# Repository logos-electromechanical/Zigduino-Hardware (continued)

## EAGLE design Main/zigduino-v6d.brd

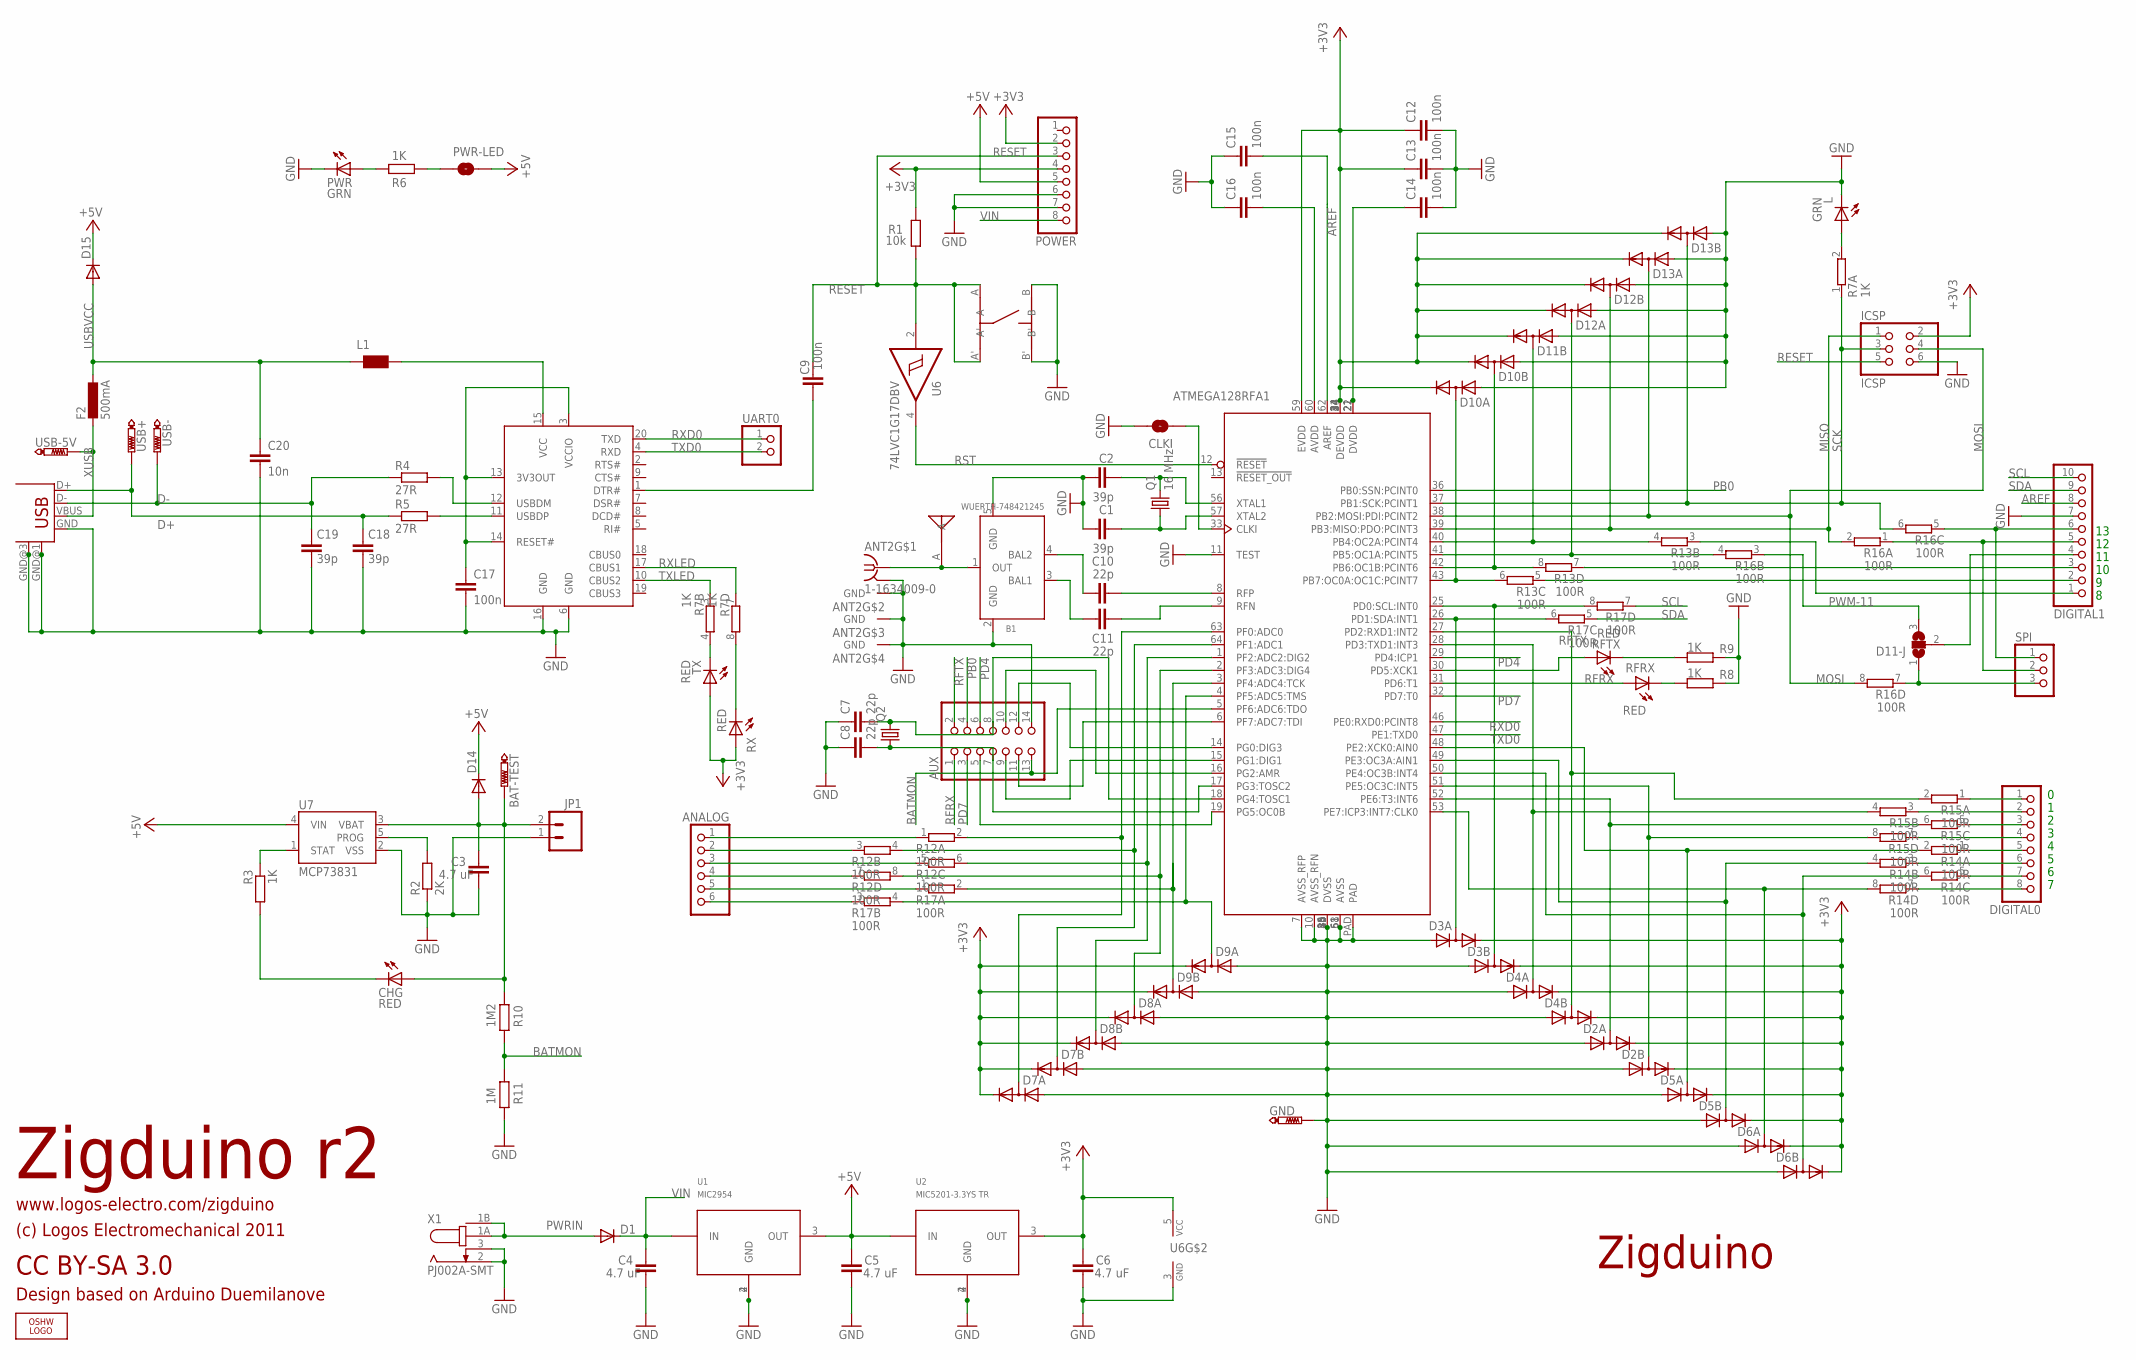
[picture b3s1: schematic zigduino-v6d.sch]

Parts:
ANALOG: PINHD-1X6; 1X06; PARTNO 19742
ANT1: MOLEX-ANT; PARTNO 0479480001
ANT2: 1-1634009-0; MMCX-THRU
AUX: PINHD-2X7_2.00; 2X07M; PARTNO 00217
B1: WUERTH-748421245; WURTH-BALUN; PARTNO 748421245
BAT-TEST: PTR1TP13SQ; TP13SQ; PARTNO TP13
C1, C2, C18, C19: 39p; C0603; PARTNO C1608C0G1H390J
C3, C4, C5, C6: 4.7 uF; C1206; PARTNO C3216Y5V1H475Z
C7, C8, C10, C11: 22p; C0603; PARTNO GQM1885C1H220JB01D
C9, C12, C13, C14, C15, C16, C17: 100n; C0603; PARTNO CC0603MRY5V9BB104
C20: 10n; C0603; PARTNO GRM188R71H103KA01D
CHG: RED; CHIP-LED0603; PARTNO LTST-C193KRKT-5A
CLKI: SOLDERJUMPERTRACE; SJ_2S-TRACE
D1, D14, D15: DIODE-SMB; SMB; PARTNO B150B-13-F
D2, D3, D4, D5, D6, D7, D8, D9, D10, D11, D12, D13: SD103ASDM; SOT26; PARTNO SD103ASDM-7
D11-J: SJ2W; SJ_2; PARTNO SJ3
DIGITAL0: PINHD-1X8; 1X08; PARTNO 19743
DIGITAL1: PINHD-1X10; 1X10; PARTNO 20083
F2: 500mA; L1812; PARTNO MF-MSMF050-2
GND: PTR1TP13SQ; TP13SQ; PARTNO TP13
ICSP: ICSP; 2X03; PARTNO 961206-6404-AR
JP1: M02-JST-2MM-SMT; S2B-PH; PARTNO S2B-PH-SM4-TB(LF)(SN)
L: GRN; CHIP-LED0603; PARTNO LTST-C193KGKT-5A
L1: WE-CBF_0805; 0805; PARTNO MI0805K400R-10
LOGO1: OSHW_LOGO_FILLX0200-NT; OSHW_FILLX200_NOTEXT
POWER: PINHD-1X8; 1X08; PARTNO 19743
PWR: GRN; CHIP-LED0603; PARTNO LTST-C193KGKT-5A
PWR-LED: SOLDERJUMPERTRACE; SJ_2S-TRACE
Q1: 16 MHz; CSM-3X; PARTNO ECS-160-20-3X-TR
Q2: CRYSTALTC26H; TC26H
R1: 10k; R0603; PARTNO RMCF0603FT10K0
R2: 2K; R0603; PARTNO RC0603FR-072KL
R3, R6, R8, R9: 1K; R0603; PARTNO RMCF0603FT1K00
R4, R5: 27R; R0603; PARTNO RC0603JR-0727RL
R7: 1K; CTS742C083-RES; PARTNO 742C083102JPTR
R10: 1M2; R0603; PARTNO ERJ-3EKF1204V
R11: 1M; R0603; PARTNO ERJ-3EKF1004V
R12, R13, R14, R15, R16, R17: 100R; CTS742C083-RES; PARTNO 742C083101JPTR
RFRX: RED; CHIP-LED0603; PARTNO LTST-C193KRKT-5A
RFTX: RED; CHIP-LED0603; PARTNO LTST-C193KRKT-5A
RX: RED; CHIP-LED0603; PARTNO LTST-C193KRKT-5A
SPI: PINHD-1X3; 1X03; PARTNO 20152
SW1: EVQ-PSD02K; EVQPSD02K; PARTNO EVQ-PSD02K
TX: RED; CHIP-LED0603; PARTNO LTST-C193KRKT-5A
U1: MIC2954; SOT223; PARTNO MIC2954-03WS-TR
U2: MIC5201-3.3YS TR; SOT223; PARTNO MIC5201-3.3YS TR
U3: ATMEGA128RFA1; QFN64; PARTNO ATMEGA128RFA1-ZUR
U4: FT231XS-R; SSOP20; PARTNO FT231XS-R
U6: 74LVC1G17DBV; SOT23-5; PARTNO SN74LVC1G17DBVR
U7: MCP73831; SOT23-5; PARTNO MCP73831T-2ACI/OT
UART0: PINHD-1X2; 1X02; PARTNO 00522
USB: USB-MB-S; PARTNO 20236
USB+: PTR1TP13SQ; TP13SQ; PARTNO TP13
USB-, USB-5V: PTR1TP13SQ; TP13SQ; PARTNO TP13
X1: PJ002A-SMT; PARTNO PJ-002AH-SMT

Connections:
+3V3: C6.1, C12.1, C13.1, D2.2 (C), D2.5 (C), D3.2 (C), D3.5 (C), D4.2 (C), D4.5 (C), D5.2 (C), D5.5 (C), D6.2 (C), D6.5 (C), D7.2 (C), D7.5 (C), D8.2 (C), D8.5 (C), D9.2 (C), D9.5 (C), D10.2 (C), D10.5 (C), D11.5 (C), D12.2 (C), D12.5 (C), D13.2 (C), D13.5 (C), ICSP.2, POWER.2, POWER.4, R1.2, RX.A, TX.A, U2.3 (OUT), U3.23 (DEVDD), U3.34 (DEVDD), U3.44 (DEVDD), U3.54 (DEVDD), U3.59 (EVDD), U6.5 (VCC)
+5V: C5.1, D14.C, D15.C, POWER.5, PWR-LED.2, U1.3 (OUT), U2.1 (IN), U7.4 (VIN)
AREF: C15.2, DIGITAL1.8, U3.62 (AREF)
BATMON: AUX.13, R10.2, R11.1, U3.5 (PF6:ADC6:TDO)
D+: C18.1, R5.1, USB.D+, USB+.TP
D-: C19.1, R4.1, USB.D-, USB-.TP
DTR: C9.1, U4.1 (DTR#)
GND: ANT2.G@0 (GND), ANT2.G@1 (GND), ANT2.G@2 (GND), ANT2.G@3 (GND), AUX.14, B1.2 (GND), B1.5 (GND), C1.1, C2.1, C3.2, C4.2, C5.2, C6.2, C7.1, C8.1, C12.2, C13.2, C14.2, C15.1, C16.1, C17.2, C18.2, C19.2, C20.2, CLKI.2, D2.3 (A), D2.6 (A), D3.3 (A), D3.6 (A), D4.3 (A), D4.6 (A), D5.3 (A), D5.6 (A), D6.3 (A), D6.6 (A), D7.3 (A), D7.6 (A), D8.3 (A), D8.6 (A), D9.3 (A), D9.6 (A), D10.3 (A), D10.6 (A), D11.6 (A), D12.3 (A), D12.6 (A), D13.3 (A), D13.6 (A), DIGITAL1.7, GND.TP, ICSP.6, JP1.1, L.C, POWER.6, POWER.7, PWR.C, R2.1, R8.1, R9.1, R11.2, SW1.B, SW1.B', U1.2 (GND), U1.4 (GND), U2.2 (GND), U2.4 (GND), U3.7 (AVSS_RFP), U3.10 (AVSS_RFN), U3.11 (TEST), U3.20 (DVSS), U3.24 (DVSS), U3.35 (DVSS), U3.45 (DVSS), U3.55 (DVSS), U3.58 (AVSS), U3.61 (AVSS), U3.PAD, U4.6 (GND), U4.16 (GND), U6.3 (GND), U7.2 (VSS), USB.GND, USB.GND@1 (GND), USB.GND@3 (GND), X1.2, X1.3
MISO: D12.1 (AC), ICSP.1, R16.2, U3.39 (PB3:MISO:PDO:PCINT3)
MOSI: D13.4 (AC), ICSP.4, R16.8 (2), U3.38 (PB2:MOSI:PDI:PCINT2)
MOSI-PIN: D11-J.1, R16.7 (1), SPI.3
unnamed: R9.2, RFTX.C
unnamed: L.A, R7.2
unnamed: PWR.A, R6.2
unnamed: B1.4 (BAL2), C10.1
unnamed: DIGITAL0.3, R15.5 (1)
unnamed: C1.2, Q1.1, U3.57 (XTAL2)
unnamed: C2.2, Q1.2, U3.56 (XTAL1)
unnamed: PWR-LED.1, R6.1
unnamed: B1.3 (BAL1), C11.1
unnamed: DIGITAL1.5, R16.1, SPI.2
unnamed: DIGITAL0.5, R14.1
unnamed: DIGITAL0.7, R14.5 (1)
unnamed: DIGITAL0.6, R14.3 (1)
unnamed: DIGITAL0.4, R15.7 (1)
unnamed: DIGITAL0.8, R14.7 (1)
unnamed: D3.1 (AC), R17.8 (2), U3.25 (PD0:SCL:INT0)
unnamed: D3.4 (AC), R17.6 (2), U3.26 (PD1:SDA:INT1)
unnamed: ANT1.A, ANT2.C (1), B1.1 (OUT)
unnamed: D12.4 (AC), R16.4 (2), U3.41 (PB5:OC1A:PCINT5)
unnamed: R8.2, RFRX.C
unnamed: D2.4 (AC), R15.6 (2), U3.52 (PE6:T3:INT6)
unnamed: D2.1 (AC), R15.8 (2), U3.51 (PE5:OC3C:INT5)
unnamed: C10.2, U3.8 (RFP)
unnamed: C11.2, U3.9 (RFN)
unnamed: DIGITAL1.6, R16.5 (1), SPI.1
unnamed: R2.2, U7.5 (PROG)
unnamed: R3.1, U7.1 (STAT)
unnamed: R7.4 (2), TX.C
unnamed: CHG.C, R3.2
unnamed: C17.1, U4.3 (VCCIO), U4.13 (3V3OUT), U4.14 (RESET#)
unnamed: R7.8 (2), RX.C
unnamed: D11.1 (AC), R13.4 (2), U3.40 (PB4:OC2A:PCINT4)
unnamed: CLKI.1, U3.33 (CLKI)
unnamed: R4.2, U4.12 (USBDM)
unnamed: R5.2, U4.11 (USBDP)
unnamed: L1.2, U4.15 (VCC)
unnamed: D10.1 (AC), R13.8 (2), U3.42 (PB6:OC1B:PCINT6)
unnamed: D10.4 (AC), R13.6 (2), U3.43 (PB7:OC0A:OC1C:PCINT7)
unnamed: D5.4 (AC), R14.2, U3.48 (PE2:XCK0:AIN0)
unnamed: D6.1 (AC), R14.6 (2), U3.50 (PE4:OC3B:INT4)
unnamed: D5.1 (AC), R14.4 (2), U3.49 (PE3:OC3A:AIN1)
unnamed: D6.4 (AC), R14.8 (2), U3.53 (PE7:ICP3:INT7:CLK0)
unnamed: ANALOG.5, R17.1
unnamed: ANALOG.6, R17.3 (1)
unnamed: AUX.11, U3.6 (PF7:ADC7:TDI)
unnamed: D7.4 (AC), R12.2, U3.63 (PF0:ADC0)
unnamed: D7.1 (AC), R12.4 (2), U3.64 (PF1:ADC1)
unnamed: D8.1 (AC), R12.6 (2), U3.1 (PF2:ADC2:DIG2)
unnamed: D8.4 (AC), R12.8 (2), U3.2 (PF3:ADC3:DIG4)
unnamed: D9.1 (AC), R17.2, U3.3 (PF4:ADC4:TCK)
unnamed: D9.4 (AC), R17.4 (2), U3.4 (PF5:ADC5:TMS)
unnamed: ANALOG.1, R12.1
unnamed: ANALOG.2, R12.3 (1)
unnamed: ANALOG.3, R12.5 (1)
unnamed: ANALOG.4, R12.7 (1)
unnamed: DIGITAL1.1, R13.3 (1)
unnamed: D11-J.2, DIGITAL1.4
unnamed: AUX.12, U3.14 (PG0:DIG3)
unnamed: C14.1, U3.21 (DVDD), U3.22 (DVDD)
unnamed: C16.2, U3.60 (AVDD)
unnamed: DIGITAL1.2, R13.5 (1)
unnamed: DIGITAL0.1, R15.1
unnamed: DIGITAL0.2, R15.3 (1)
unnamed: AUX.9, U3.15 (PG1:DIG1)
unnamed: AUX.5, U3.19 (PG5:OC0B)
unnamed: AUX.8, C7.2, Q2.2, U3.18 (PG4:TOSC1)
unnamed: AUX.7, C8.2, Q2.1, U3.17 (PG3:TOSC2)
unnamed: AUX.10, U3.16 (PG2:AMR)
PB0: AUX.4, U3.36 (PB0:SSN:PCINT0)
PD4: AUX.6, U3.29 (PD4:ICP1)
PD7: AUX.3, U3.32 (PD7:T0)
PWM-10: DIGITAL1.3, R13.7 (1)
PWM-11: D11-J.3, R16.3 (1)
PWRIN: D1.A, X1.1A, X1.1B
RESET: C9.2, ICSP.5, POWER.3, R1.1, SW1.A, SW1.A', U6.2 (I)
RFRX: AUX.1, RFRX.A, U3.31 (PD6:T1)
RFTX: AUX.2, RFTX.A, U3.30 (PD5:XCK1)
RST: U3.12 (!RESET!), U6.4 (O)
RXD0: U3.46 (PE0:RXD0:PCINT8), U4.20 (TXD), UART0.1
RXD1: D4.1 (AC), R15.2, U3.27 (PD2:RXD1:INT2)
RXLED: R7.7 (1), U4.17 (CBUS1)
SCK: D13.1 (AC), ICSP.3, R7.1, R16.6 (2), U3.37 (PB1:SCK:PCINT1)
SCL: DIGITAL1.10, R17.7 (1)
SDA: DIGITAL1.9, R17.5 (1)
TXD0: U3.47 (PE1:TXD0), U4.4 (RXD), UART0.2
TXD1: D4.4 (AC), R15.4 (2), U3.28 (PD3:TXD1:INT3)
TXLED: R7.3 (1), U4.10 (CBUS2)
USBVCC: C20.1, D15.A, F2.1, L1.1
VBAT: BAT-TEST.TP, C3.1, CHG.A, D14.A, JP1.2, R10.1, U7.3 (VBAT)
VIN: C4.1, D1.C, POWER.8, U1.1 (IN)
XUSB: F2.2, USB.VBUS, USB-5V.TP

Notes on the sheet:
Zigduino r2
CC BY-SA 3.0
(c) Logos Electromechanical 2011
www.logos-electro.com/zigduino
ATMEGA128RFA1
Zigduino
Design based on Arduino Duemilanove

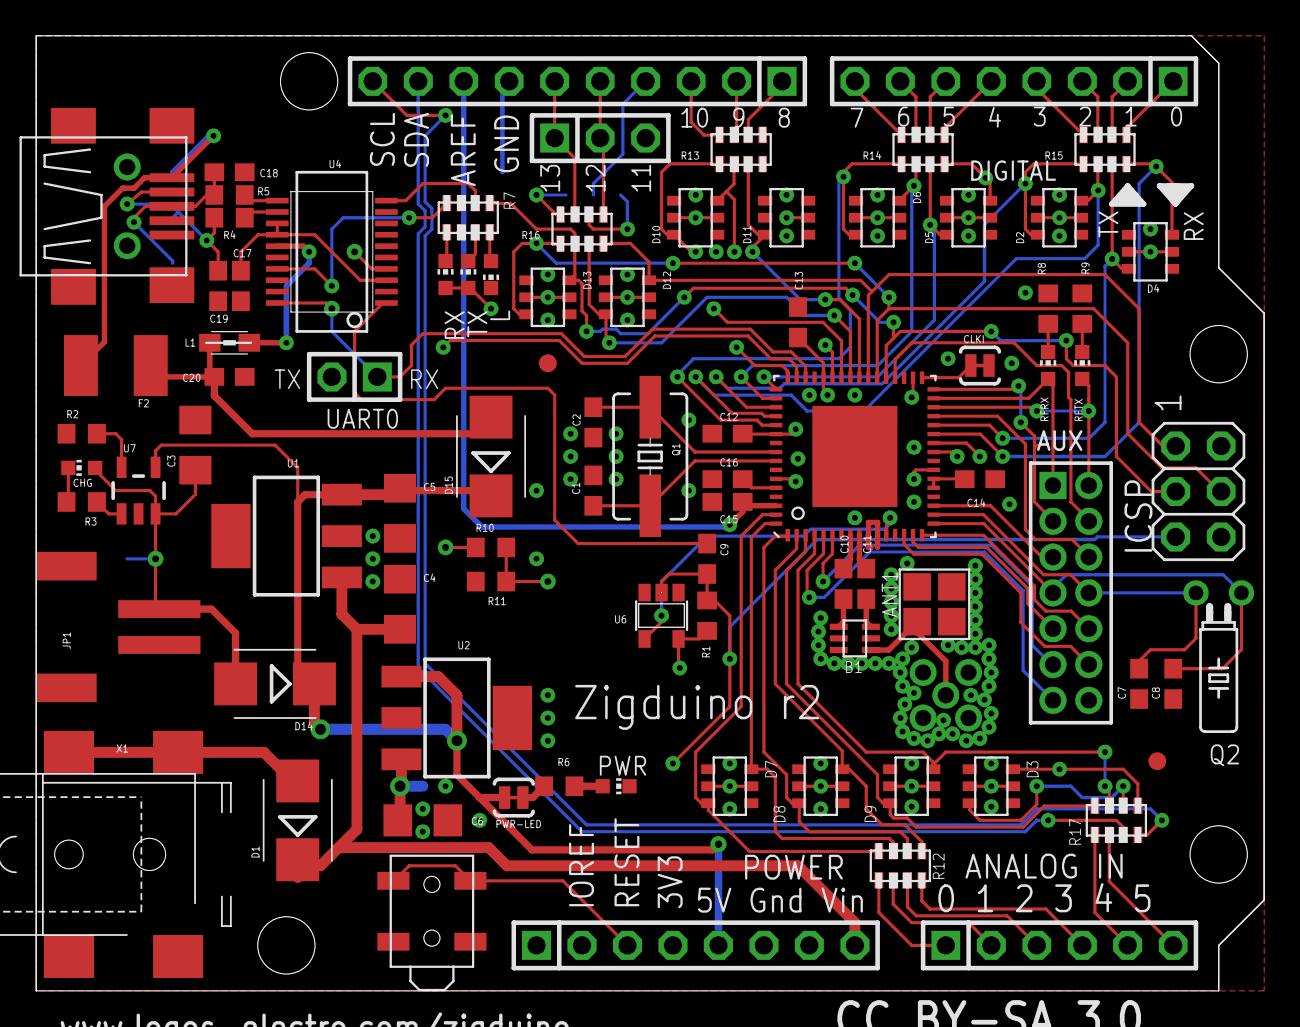
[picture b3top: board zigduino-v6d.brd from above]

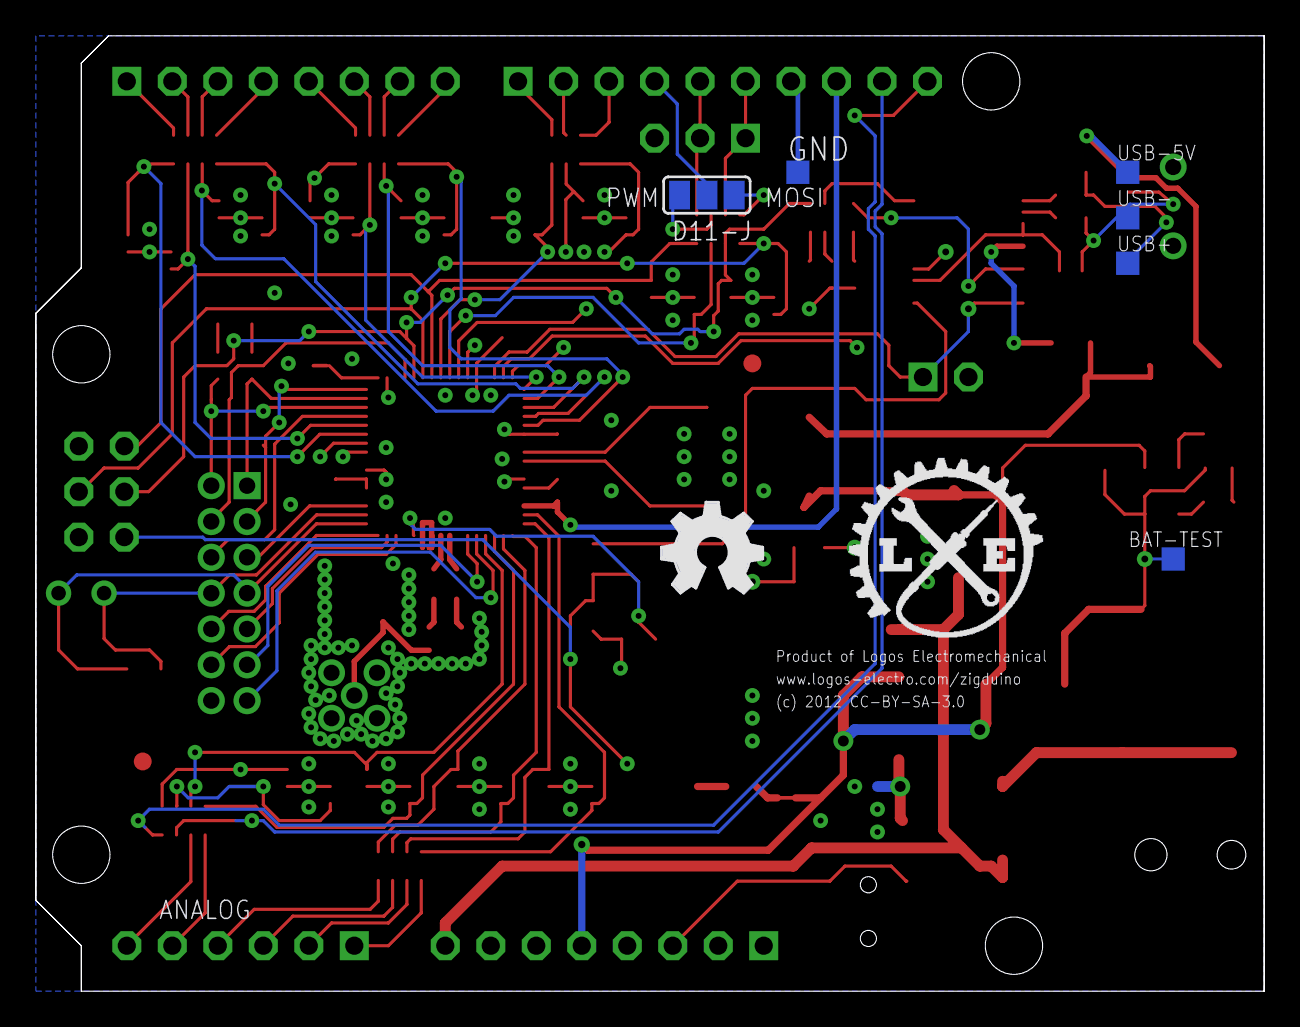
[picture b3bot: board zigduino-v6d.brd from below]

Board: 4 copper layers, 68.6 x 53.3 mm, 96 parts (8 on the bottom side), 102 nets.

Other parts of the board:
U$3, U$5: FIDUCIAL_G10
U$4: LOGO-SM

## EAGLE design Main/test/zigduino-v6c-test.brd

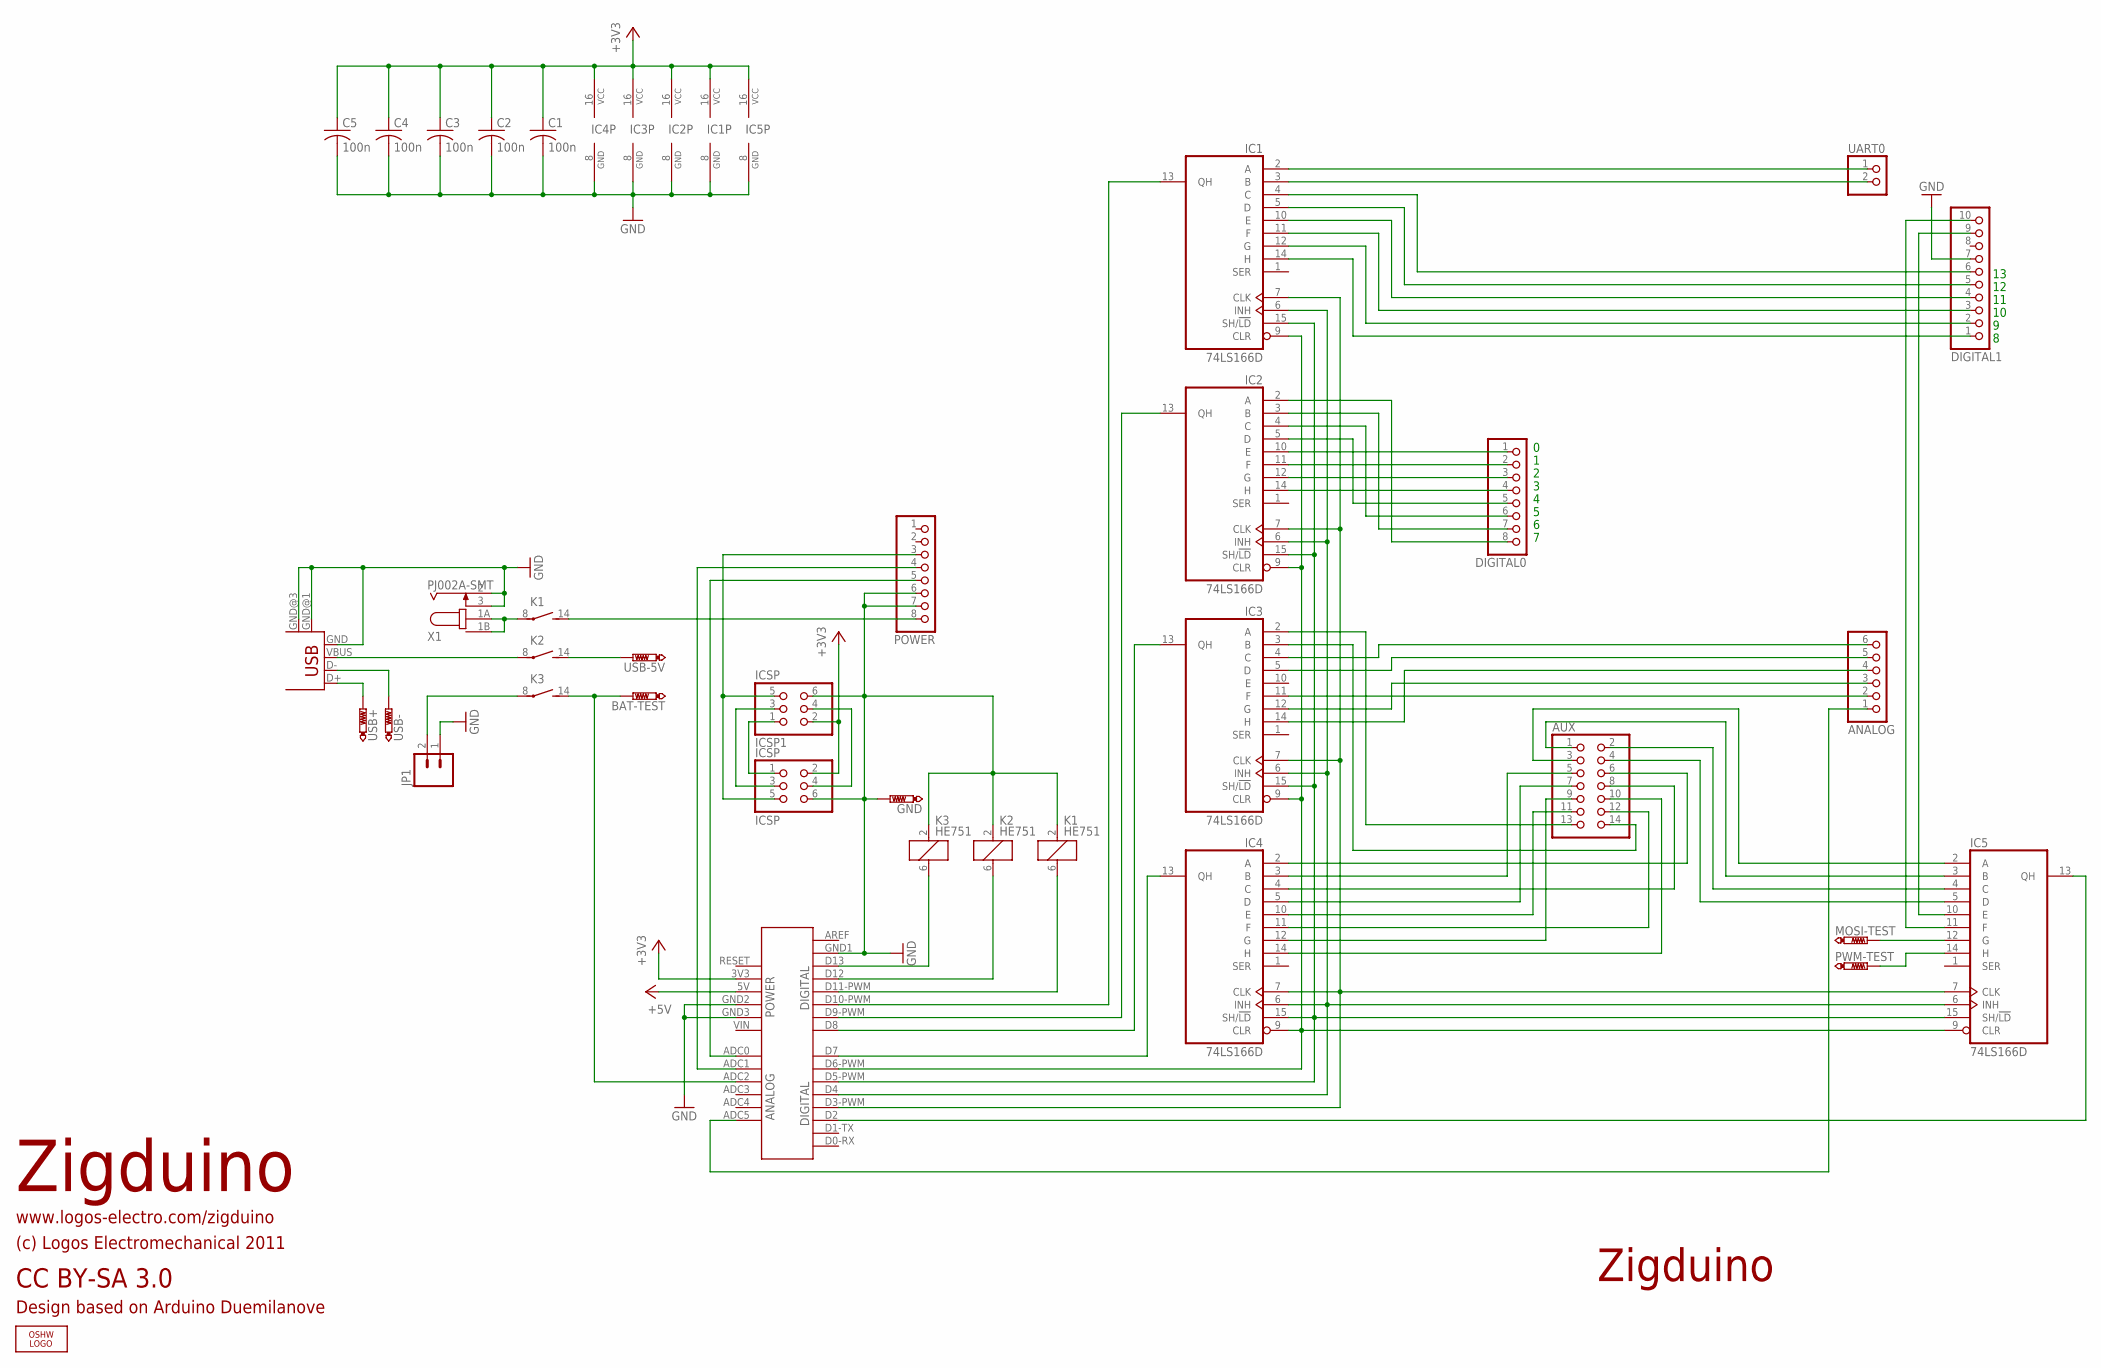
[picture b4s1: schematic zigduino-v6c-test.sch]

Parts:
ANALOG: PINHD-1X6; 1X06; PARTNO 19742
AUX: PINHD-2X7_2.00; 2X07M; PARTNO 00217
BAT-TEST: PTR1PAD1-13; P1-13; PARTNO TP13
C1, C2, C3, C4, C5: 100n; C0603
DIGITAL0: PINHD-1X8; 1X08; PARTNO 19743
DIGITAL1: PINHD-1X10; 1X10; PARTNO 20083
GND: PTR1PAD1-13; P1-13; PARTNO TP13
IC1, IC2, IC3, IC4, IC5: 74LS166D; SO16
ICSP, ICSP1: ICSP; 2X03; PARTNO 961206-6404-AR
JP1: M02-JST-2MM-SMT; S2B-PH
K1, K2, K3: HE751
LOGO1: OSHW_LOGO_FILLX0200-NT; OSHW_FILLX200_NOTEXT
MOSI-TEST: PTR1PAD1-13; P1-13; PARTNO TP13
POWER: PINHD-1X8; 1X08; PARTNO 19743
PWM-TEST: PTR1PAD1-13; P1-13; PARTNO TP13
SHIELD1: 2009
UART0: PINHD-1X2; 1X02; PARTNO 00522
USB1: USB-MB-S
USB+: PTR1PAD1-13; P1-13; PARTNO TP13
USB-, USB-5V: PTR1PAD1-13; P1-13; PARTNO TP13
X1: PJ002A-SMT

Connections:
+3V3: C1.1, C2.1, C3.1, C4.1, C5.1, IC1.16 (VCC), IC2.16 (VCC), IC3.16 (VCC), IC4.16 (VCC), IC5.16 (VCC), ICSP.2, ICSP1.2, SHIELD1.3V3
+5V: SHIELD1.5V
GND: C1.2, C2.2, C3.2, C4.2, C5.2, DIGITAL1.7, GND.TP, IC1.8 (GND), IC2.8 (GND), IC3.8 (GND), IC4.8 (GND), IC5.8 (GND), ICSP.6, ICSP1.6, JP1.1, K1.2 (1), K2.2 (1), K3.2 (1), POWER.6, POWER.7, SHIELD1.GND1, SHIELD1.GND2, SHIELD1.GND3, USB1.GND, USB1.GND@1 (GND), USB1.GND@3 (GND), X1.2, X1.3
unnamed: IC1.2 (A), UART0.1
unnamed: IC1.3 (B), UART0.2
unnamed: JP1.2, K3.8
unnamed: DIGITAL1.6, IC1.4 (C)
unnamed: DIGITAL1.5, IC1.5 (D)
unnamed: DIGITAL1.4, IC1.10 (E)
unnamed: DIGITAL1.3, IC1.11 (F)
unnamed: DIGITAL1.2, IC1.12 (G)
unnamed: DIGITAL1.1, IC1.14 (H)
unnamed: DIGITAL0.4, IC2.14 (H)
unnamed: DIGITAL0.3, IC2.12 (G)
unnamed: DIGITAL0.2, IC2.11 (F)
unnamed: DIGITAL0.1, IC2.10 (E)
unnamed: DIGITAL0.5, IC2.5 (D)
unnamed: DIGITAL0.6, IC2.4 (C)
unnamed: DIGITAL0.7, IC2.3 (B)
unnamed: DIGITAL0.8, IC2.2 (A)
unnamed: ANALOG.1, SHIELD1.ADC5
unnamed: ANALOG.6, IC3.4 (C)
unnamed: ANALOG.5, IC3.5 (D)
unnamed: ANALOG.4, IC3.14 (H)
unnamed: ANALOG.3, IC3.12 (G)
unnamed: ANALOG.2, IC3.11 (F)
unnamed: AUX.13, IC3.2 (A)
unnamed: AUX.14, IC3.3 (B)
unnamed: AUX.6, IC4.2 (A)
unnamed: AUX.5, IC4.3 (B)
unnamed: AUX.8, IC4.4 (C)
unnamed: AUX.7, IC4.5 (D)
unnamed: AUX.11, IC4.10 (E)
unnamed: AUX.12, IC4.11 (F)
unnamed: AUX.9, IC4.12 (G)
unnamed: AUX.3, IC5.2 (A)
unnamed: AUX.10, IC4.14 (H)
unnamed: AUX.2, IC5.4 (C)
unnamed: AUX.4, IC5.5 (D)
unnamed: AUX.1, IC5.3 (B)
unnamed: IC1.9 (CLR), IC2.9 (CLR), IC3.9 (CLR), IC4.9 (CLR), IC5.9 (CLR), SHIELD1.D6-PWM (D6)
unnamed: IC1.15 (SH/!LD), IC2.15 (SH/!LD), IC3.15 (SH/!LD), IC4.15 (SH/!LD), IC5.15 (SH/!LD), SHIELD1.D5-PWM (D5)
unnamed: IC1.6 (INH), IC2.6 (INH), IC3.6 (INH), IC4.6 (INH), IC5.6 (INH), SHIELD1.D4
unnamed: IC1.7 (CLK), IC2.7 (CLK), IC3.7 (CLK), IC4.7 (CLK), IC5.7 (CLK), SHIELD1.D3-PWM (D3)
unnamed: DIGITAL1.9, IC5.10 (E)
unnamed: DIGITAL1.10, IC5.11 (F)
unnamed: IC5.12 (G), MOSI-TEST.TP
unnamed: IC5.14 (H), PWM-TEST.TP
unnamed: IC1.13 (QH), SHIELD1.D10-PWM (D10)
unnamed: IC2.13 (QH), SHIELD1.D9-PWM (D9)
unnamed: IC3.13 (QH), SHIELD1.D8
unnamed: IC4.13 (QH), SHIELD1.D7
unnamed: IC5.13 (QH), SHIELD1.D2
unnamed: POWER.5, SHIELD1.ADC0
unnamed: POWER.4, SHIELD1.ADC1
unnamed: K1.14 (S), POWER.8
unnamed: K2.14 (S), USB-5V.TP
unnamed: BAT-TEST.TP, K3.14 (S), SHIELD1.ADC2
unnamed: K2.6 (2), SHIELD1.D12
unnamed: K1.6 (2), SHIELD1.D11-PWM (D11)
unnamed: ICSP.4, ICSP1.4
unnamed: K3.6 (2), SHIELD1.D13
unnamed: ICSP.1, ICSP1.1
unnamed: ICSP.3, ICSP1.3
unnamed: ICSP.5, ICSP1.5, POWER.3
unnamed: K2.8, USB1.VBUS
unnamed: USB1.D+, USB+.TP
unnamed: USB1.D-, USB-.TP
unnamed: K1.8, X1.1A, X1.1B

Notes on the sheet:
Zigduino
CC BY-SA 3.0
(c) Logos Electromechanical 2011
www.logos-electro.com/zigduino
Design based on Arduino Duemilanove

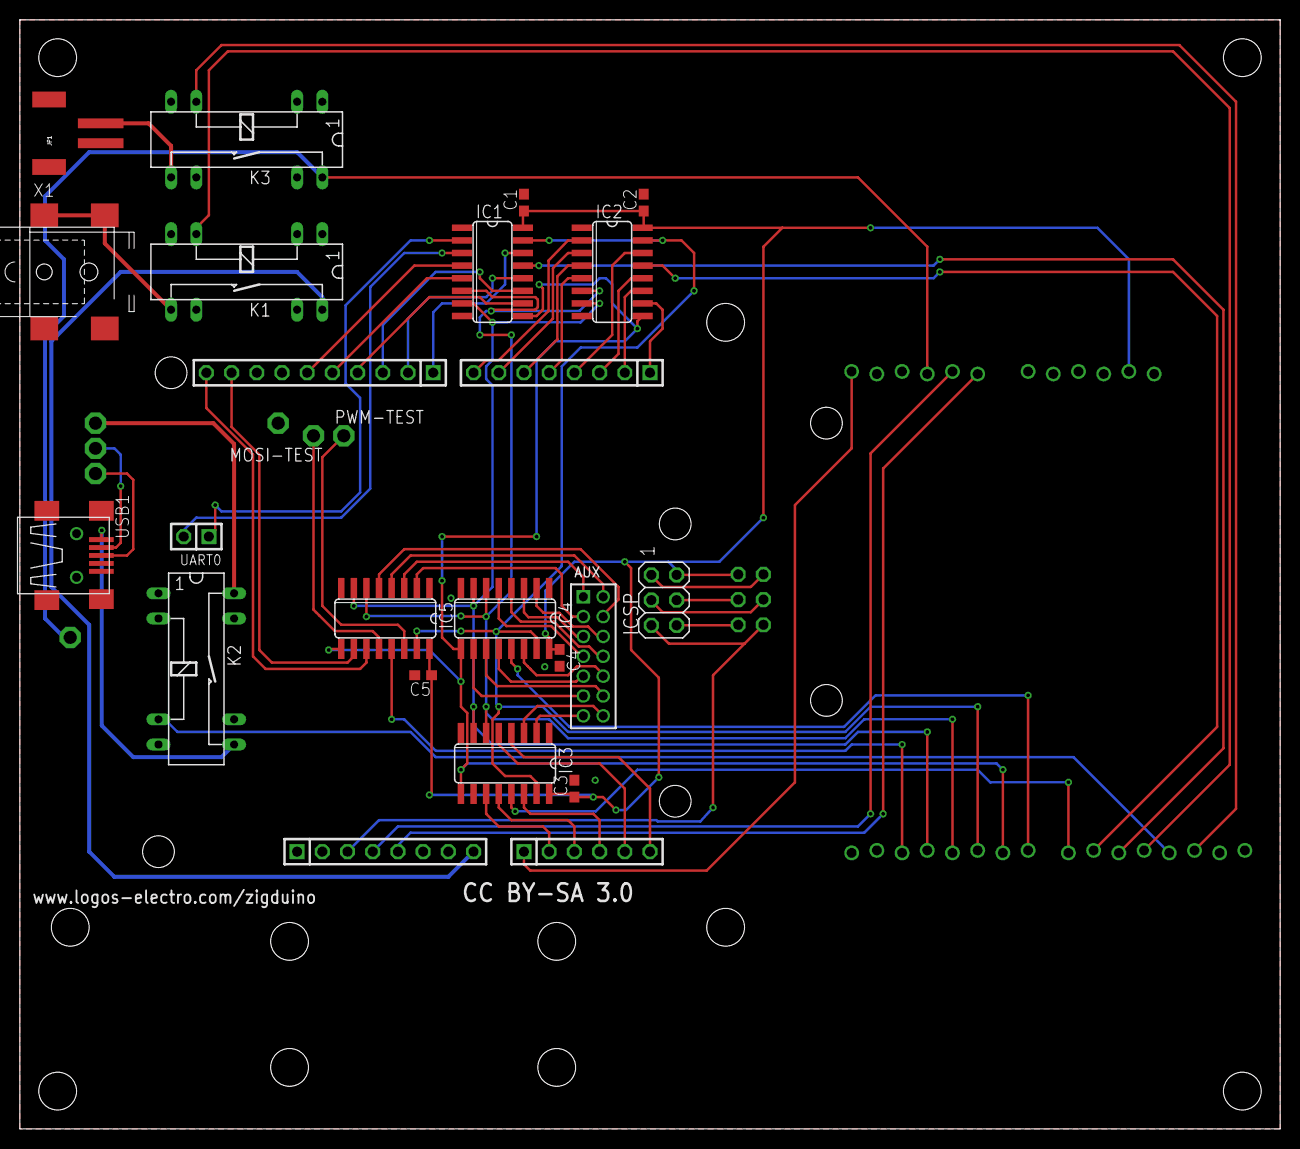
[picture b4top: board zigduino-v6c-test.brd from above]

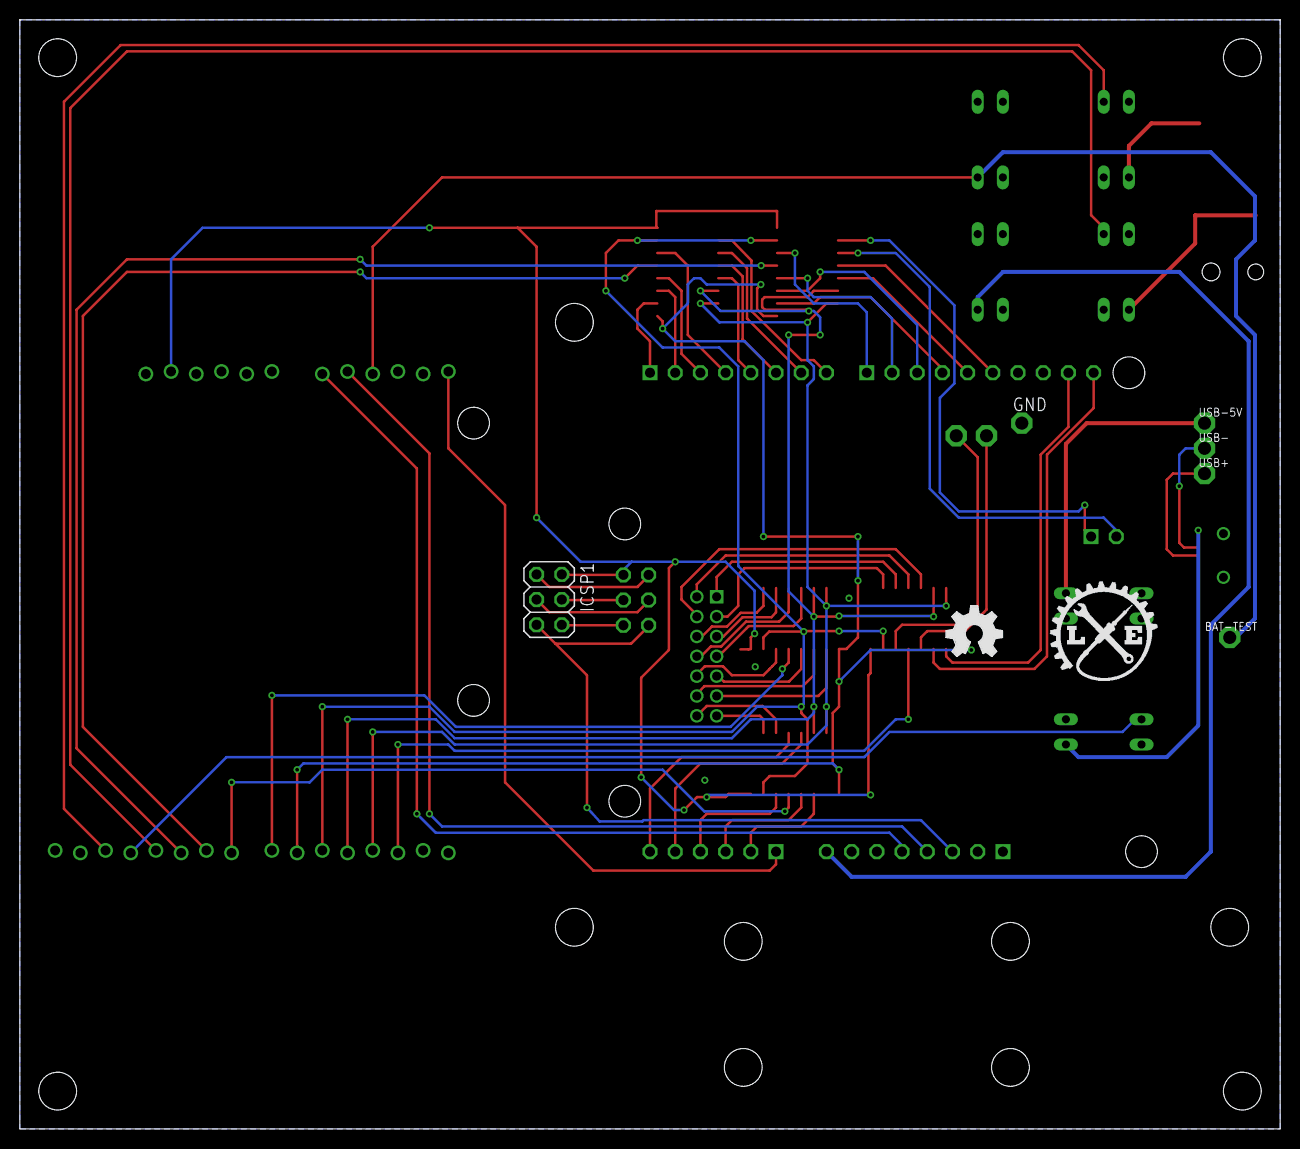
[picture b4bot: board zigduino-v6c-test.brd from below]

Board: 2 copper layers, 127.0 x 111.8 mm, 34 parts (8 on the bottom side), 68 nets.

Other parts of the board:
U$4: LOGO-SM

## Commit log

2013-02-24 Checking in all of the current Zigduino files to the new repository.
2013-02-24 Checking in existing Zigduino Mote work
2013-02-24 Seems the last commit lost the updated .gitignore
2013-02-27 -- Checking in v6d files (aka Zigduino r2, spin 2) files -- Starting Esplora directory
2013-06-12 Moved things around to create the Zigduino Micro
2013-06-16 -- Changed .gitignore to ignore various generated files -- Created Zigduino Micro
2013-12-27 added Zigduino Micro files updated burning instructions added Zigduino r3 files
